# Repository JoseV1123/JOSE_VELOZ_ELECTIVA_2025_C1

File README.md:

# JOSE_VELOZ_ELECTIVA_2025_C1
Repositorio de la materia Electiva Mecatrónica 2025-C1.

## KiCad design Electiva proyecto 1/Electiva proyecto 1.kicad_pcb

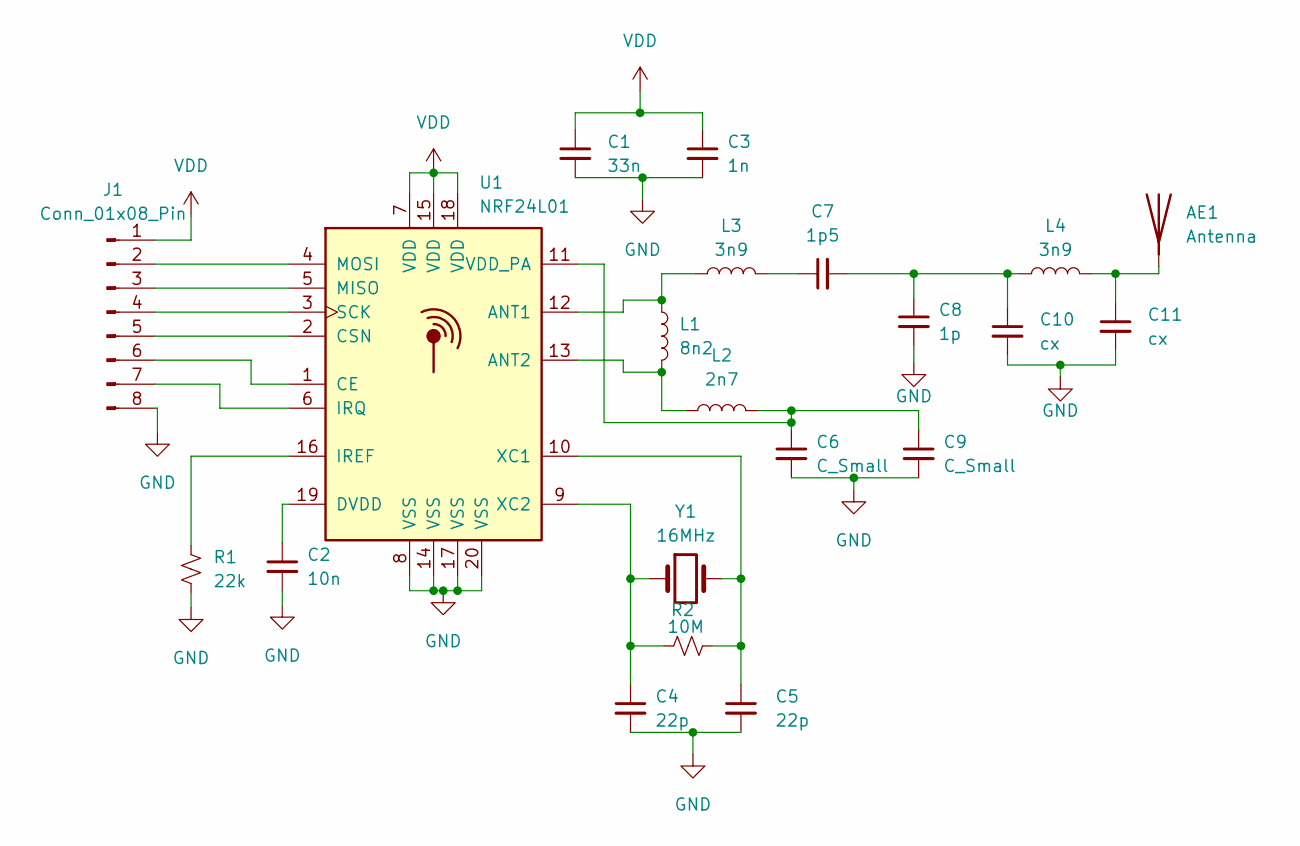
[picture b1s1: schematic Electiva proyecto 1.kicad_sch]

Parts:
AE1: Antenna; Texas_SWRA117D_2.4GHz_Right
C1: 33n; C_0402_1005Metric
C2: 10n; C_0402_1005Metric
C3: 1n; C_0402_1005Metric
C4, C5: 22p; C_0402_1005Metric
C6, C9: C_Small; C_0402_1005Metric
C7: 1p5; C_0402_1005Metric
C8: 1p; C_0402_1005Metric
C10, C11: cx; C_0402_1005Metric
J1: Conn_01x08_Pin; Hirose_DF13-08P-1.25DSA_1x08_P1.25mm_Vertical
L1: 8n2; L_0402_1005Metric
L2: 2n7; L_0402_1005Metric
L3, L4: 3n9; L_0402_1005Metric
R1: 22k; R_0402_1005Metric
R2: 10M; R_0402_1005Metric
U1: NRF24L01; QFN-20-1EP_4x4mm_P0.5mm_EP2.5x2.5mm
Y1: 16MHz; Crystal_SMD_3215-2Pin_3.2x1.5mm

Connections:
GND: C1.2, C2.2, C3.2, C4.2, C5.2, C6.2, C8.2, C9.2, C10.2, C11.2, J1.8, R1.2, U1.8 (VSS), U1.14 (VSS), U1.17 (VSS), U1.20 (VSS)
unnamed: AE1.1 (A), C11.1, L4.2
unnamed: C7.1, L3.2
unnamed: C7.2, C8.1, C10.1, L4.1
unnamed: J1.2, U1.4 (MOSI)
unnamed: J1.3, U1.5 (MISO)
unnamed: J1.4, U1.3 (SCK)
unnamed: J1.5, U1.2 (CSN)
unnamed: J1.6, U1.1 (CE)
unnamed: J1.7, U1.6 (IRQ)
unnamed: L1.1, L3.1, U1.12 (ANT1)
unnamed: L1.2, L2.1, U1.13 (ANT2)
unnamed: C2.1, U1.19 (DVDD)
unnamed: R1.1, U1.16 (IREF)
unnamed: C6.1, C9.1, L2.2, U1.11 (VDD_PA)
unnamed: C5.1, R2.2, U1.10 (XC1), Y1.2
unnamed: C4.1, R2.1, U1.9 (XC2), Y1.1
VDD: C1.1, C3.1, J1.1, U1.7 (VDD), U1.15 (VDD), U1.18 (VDD)

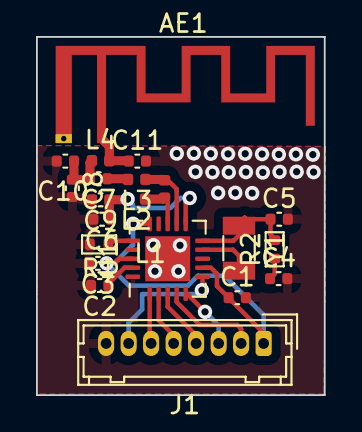
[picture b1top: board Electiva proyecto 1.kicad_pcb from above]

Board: 2 copper layers, 16.0 x 19.9 mm, 21 parts (0 on the bottom side), 18 nets.

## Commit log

2025-01-23 Tarea 1/NRF24L01
2025-03-21 practica ll pcb
2025-04-11 Practica 2 sin errores
    La otra no quiere abrir y no se guardo bien
2025-04-25 Ultimo proyecto
    freecad
2025-04-25 Ultimo proyecto
    subido en solid edge
